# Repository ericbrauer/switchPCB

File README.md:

# switchPCB
A small generic PCB to be used with 3PDT footswitches used in guitar pedals

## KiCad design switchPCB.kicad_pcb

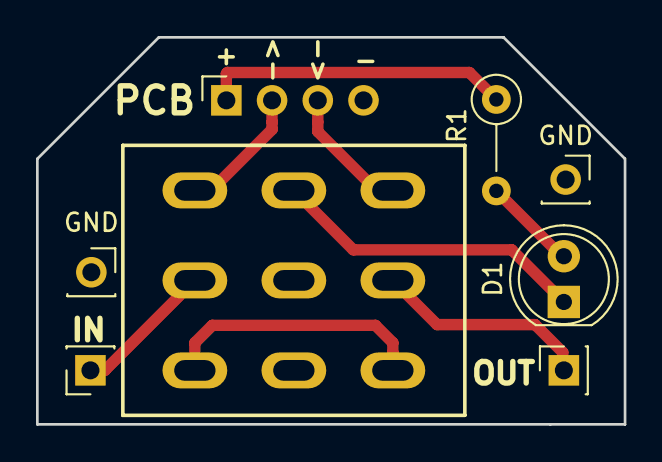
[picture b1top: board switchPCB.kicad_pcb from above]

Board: 2 copper layers, 32.7 x 21.5 mm, 8 parts (1 on the bottom side), 9 nets.

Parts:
D1: LED; LED_D5.0mm
GND: PinSocket_1x01_P2.54mm_Vertical
GND#2: PinSocket_1x01_P2.54mm_Vertical
J1, J2: Conn_01x02_Female; PinSocket_1x01_P2.54mm_Vertical
J3: Conn_01x04_Female; PinSocket_1x04_P2.54mm_Vertical
R1: 220; R_Axial_DIN0207_L6.3mm_D2.5mm_P5.08mm_Vertical
SW1: SW_3PDT_x3; 3PDT-footswitch-lugged

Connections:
GND: GND.1, GND#2.1, J3.4, SW1.5
unnamed: D1.1, SW1.6
unnamed: D1.2, R1.2
unnamed: J1.1, SW1.2
unnamed: J2.1, SW1.8
unnamed: J3.1, R1.1
unnamed: J3.2, SW1.3
unnamed: J3.3, SW1.9
unnamed: SW1.1, SW1.7

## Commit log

2019-06-06 footprint and schematic added
2019-06-06 first pcb design
2019-06-06 increasing drill hole size on 3pdt sw footprint
2021-05-01 LED on the out side
